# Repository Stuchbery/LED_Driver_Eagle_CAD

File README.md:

# LED_Driver_Eagle_CAD
Led Driver for Light Tower Project

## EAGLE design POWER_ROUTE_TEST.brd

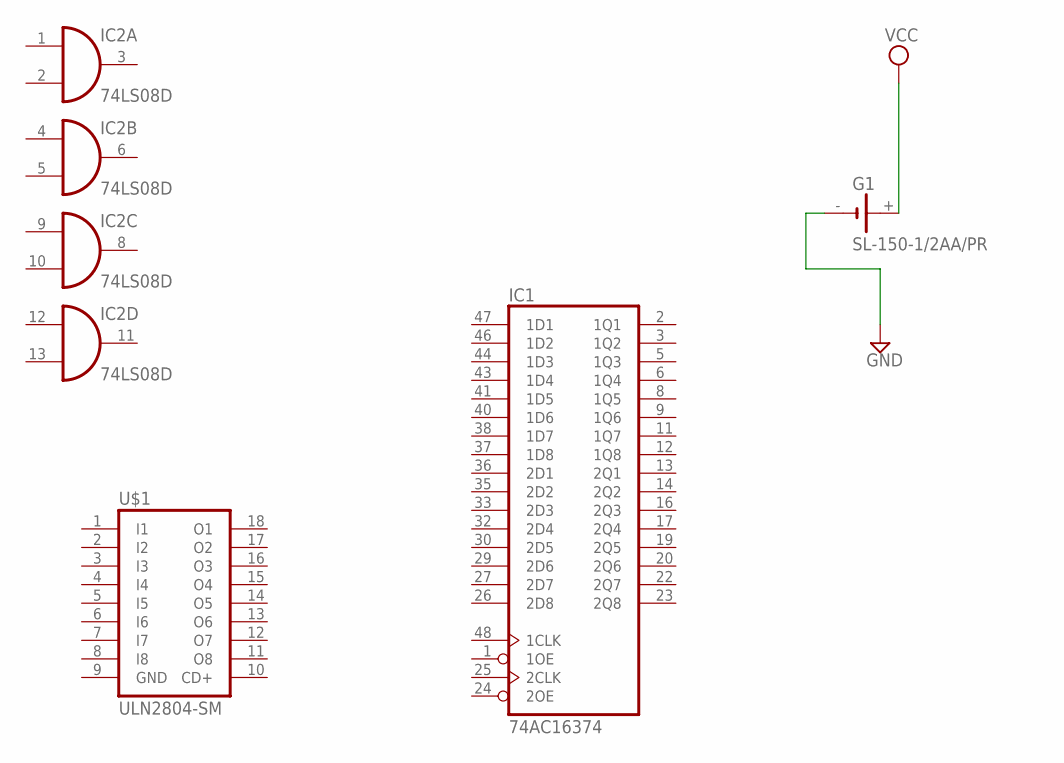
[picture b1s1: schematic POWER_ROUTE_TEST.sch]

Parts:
G1: SL-150-1/2AA/PR
IC1: 74AC16374; SSOP48DL
IC2: 74LS08D; SO14
U$1: ULN2804-SM; SOP-18

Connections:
GND: G1.-, IC1.4 (GND), IC1.10 (GND), IC1.15 (GND), IC1.21 (GND), IC1.28 (GND), IC1.34 (GND), IC1.39 (GND), IC1.45 (GND), IC2.7 (GND), U$1.9 (GND)
VCC: G1.+, IC1.7 (VCC), IC1.18 (VCC), IC1.31 (VCC), IC1.42 (VCC), IC2.14 (VCC)

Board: 2 copper layers, 4 parts (0 on the bottom side), 2 nets, no tracks yet.

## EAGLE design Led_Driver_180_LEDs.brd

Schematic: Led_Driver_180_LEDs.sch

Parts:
IC1, IC3, IC8, IC16, IC21, IC26, IC41, IC46, IC51, IC56, IC101, IC102: 74AC16374; SSOP48DL
IC2, IC4, IC5, IC6, IC7, IC9, IC10, IC11, IC12, IC13, IC14, IC15, IC17, IC18, IC19, IC20, IC22, IC23, IC24, IC25, IC27, IC28, IC29, IC30, IC42, IC43, IC44, IC45, IC47, IC48, IC49, IC50, IC52, IC53, IC54, IC55, IC57, IC58, IC59, IC60: 74S08D; SO14
U$1, U$2, U$3, U$4, U$5, U$6, U$7, U$8, U$9, U$10, U$11, U$12, U$17, U$18, U$19, U$20, U$21, U$22, U$23, U$24: ULN2804-SM; SOP-18
X1, X2, X3, X5, X6: 87758-3216
X11: 87758-1416

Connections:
GND: IC1.1 (1OE), IC1.4 (GND), IC1.10 (GND), IC1.15 (GND), IC1.21 (GND), IC1.24 (2OE), IC1.28 (GND), IC1.34 (GND), IC1.39 (GND), IC1.45 (GND), IC2.7 (GND), IC3.1 (1OE), IC3.4 (GND), IC3.10 (GND), IC3.15 (GND), IC3.21 (GND), IC3.24 (2OE), IC3.28 (GND), IC3.34 (GND), IC3.39 (GND), IC3.45 (GND), IC4.7 (GND), IC5.7 (GND), IC6.7 (GND), IC7.7 (GND), IC8.1 (1OE), IC8.4 (GND), IC8.10 (GND), IC8.15 (GND), IC8.21 (GND), IC8.24 (2OE), IC8.28 (GND), IC8.34 (GND), IC8.39 (GND), IC8.45 (GND), IC9.7 (GND), IC10.7 (GND), IC11.7 (GND), IC12.7 (GND), IC13.7 (GND), IC14.7 (GND), IC15.7 (GND), IC16.1 (1OE), IC16.4 (GND), IC16.10 (GND), IC16.15 (GND), IC16.21 (GND), IC16.24 (2OE), IC16.28 (GND), IC16.34 (GND), IC16.39 (GND), IC16.45 (GND), IC17.7 (GND), IC18.7 (GND), IC19.7 (GND), IC20.7 (GND), IC21.1 (1OE), IC21.4 (GND), IC21.10 (GND), IC21.15 (GND), IC21.21 (GND), IC21.24 (2OE), IC21.28 (GND), IC21.34 (GND), IC21.39 (GND), IC21.45 (GND), IC22.7 (GND), IC23.7 (GND), IC24.7 (GND), IC25.7 (GND), IC26.1 (1OE), IC26.4 (GND), IC26.10 (GND), IC26.15 (GND), IC26.21 (GND), IC26.24 (2OE), IC26.28 (GND), IC26.34 (GND), IC26.39 (GND), IC26.45 (GND), IC27.7 (GND), IC28.7 (GND), IC29.7 (GND), IC30.7 (GND), IC41.1 (1OE), IC41.4 (GND), IC41.10 (GND), IC41.15 (GND), IC41.21 (GND), IC41.24 (2OE), IC41.28 (GND), IC41.34 (GND), IC41.39 (GND), IC41.45 (GND), IC42.7 (GND), IC43.7 (GND), IC44.7 (GND), IC45.7 (GND), IC46.1 (1OE), IC46.4 (GND), IC46.10 (GND), IC46.15 (GND), IC46.21 (GND), IC46.24 (2OE), IC46.28 (GND), IC46.34 (GND), IC46.39 (GND), IC46.45 (GND), IC47.7 (GND), IC48.7 (GND), IC49.7 (GND), IC50.7 (GND), IC51.1 (1OE), IC51.4 (GND), IC51.10 (GND), IC51.15 (GND), IC51.21 (GND), IC51.24 (2OE), IC51.28 (GND), IC51.34 (GND), IC51.39 (GND), IC51.45 (GND), IC52.7 (GND), IC53.7 (GND), IC54.7 (GND), IC55.7 (GND), IC56.1 (1OE), IC56.4 (GND), IC56.10 (GND), IC56.15 (GND), IC56.21 (GND), IC56.24 (2OE), IC56.28 (GND), IC56.34 (GND), IC56.39 (GND), IC56.45 (GND), IC57.7 (GND), IC58.7 (GND), IC59.7 (GND), IC60.7 (GND), IC101.1 (1OE), IC101.4 (GND), IC101.10 (GND), IC101.15 (GND), IC101.21 (GND), IC101.24 (2OE), IC101.28 (GND), IC101.34 (GND), IC101.39 (GND), IC101.45 (GND), IC102.1 (1OE), IC102.4 (GND), IC102.10 (GND), IC102.15 (GND), IC102.21 (GND), IC102.24 (2OE), IC102.28 (GND), IC102.34 (GND), IC102.39 (GND), IC102.45 (GND), U$1.9 (GND), U$2.9 (GND), U$3.9 (GND), U$4.9 (GND), U$5.9 (GND), U$6.9 (GND), U$7.9 (GND), U$8.9 (GND), U$9.9 (GND), U$10.9 (GND), U$11.9 (GND), U$12.9 (GND), U$17.9 (GND), U$18.9 (GND), U$19.9 (GND), U$20.9 (GND), U$21.9 (GND), U$22.9 (GND), U$23.9 (GND), U$24.9 (GND), X11.9
unnamed: IC46.23 (2Q8), IC50.12 (I0), X11.2
unnamed: IC1.2 (1Q1), IC1.46 (1D2), IC2.1 (I0)
unnamed: IC1.3 (1Q2), IC1.44 (1D3), IC2.4 (I0)
unnamed: IC1.5 (1Q3), IC1.43 (1D4), IC2.9 (I0)
unnamed: IC1.6 (1Q4), IC1.41 (1D5), IC2.12 (I0)
unnamed: IC1.8 (1Q5), IC1.40 (1D6), IC4.1 (I0)
unnamed: IC1.9 (1Q6), IC1.38 (1D7), IC4.4 (I0)
unnamed: IC1.11 (1Q7), IC1.37 (1D8), IC4.9 (I0)
unnamed: IC1.12 (1Q8), IC1.36 (2D1), IC4.12 (I0)
unnamed: IC1.13 (2Q1), IC1.35 (2D2), IC5.1 (I0)
unnamed: IC1.14 (2Q2), IC1.33 (2D3), IC5.4 (I0)
unnamed: IC1.16 (2Q3), IC1.32 (2D4), IC5.9 (I0)
unnamed: IC1.17 (2Q4), IC1.30 (2D5), IC5.12 (I0)
unnamed: IC1.19 (2Q5), IC1.29 (2D6), IC6.1 (I0)
unnamed: IC1.20 (2Q6), IC1.27 (2D7), IC6.4 (I0)
unnamed: IC1.22 (2Q7), IC1.26 (2D8), IC6.9 (I0)
unnamed: U$1.18 (O1), X2.1
unnamed: IC2.3 (O), U$1.1 (I1)
unnamed: IC2.6 (O), U$1.2 (I2)
unnamed: IC2.8 (O), U$1.3 (I3)
unnamed: IC2.11 (O), U$1.4 (I4)
unnamed: IC4.3 (O), U$1.5 (I5)
unnamed: IC4.11 (O), U$1.8 (I8)
unnamed: IC4.8 (O), U$1.7 (I7)
unnamed: IC4.6 (O), U$1.6 (I6)
unnamed: IC5.3 (O), U$2.1 (I1)
unnamed: IC5.6 (O), U$2.2 (I2)
unnamed: IC5.8 (O), U$2.3 (I3)
unnamed: IC6.11 (O), U$2.8 (I8)
unnamed: IC6.8 (O), U$2.7 (I7)
unnamed: IC6.6 (O), U$2.6 (I6)
unnamed: IC6.3 (O), U$2.5 (I5)
unnamed: IC5.11 (O), U$2.4 (I4)
unnamed: IC22.2 (I1), IC22.5 (I1), IC22.10 (I1), IC22.13 (I1), IC23.2 (I1), IC23.5 (I1), IC23.10 (I1), IC23.13 (I1), IC101.2 (1Q1), IC101.46 (1D2)
unnamed: IC24.2 (I1), IC24.5 (I1), IC24.10 (I1), IC24.13 (I1), IC25.2 (I1), IC25.5 (I1), IC25.10 (I1), IC25.13 (I1), IC101.3 (1Q2), IC101.44 (1D3)
unnamed: IC8.2 (1Q1), IC8.46 (1D2), IC9.1 (I0)
unnamed: IC8.3 (1Q2), IC8.44 (1D3), IC9.4 (I0)
unnamed: IC8.5 (1Q3), IC8.43 (1D4), IC9.9 (I0)
unnamed: IC8.6 (1Q4), IC8.41 (1D5), IC9.12 (I0)
unnamed: IC8.8 (1Q5), IC8.40 (1D6), IC11.1 (I0)
unnamed: IC8.9 (1Q6), IC8.38 (1D7), IC11.4 (I0)
unnamed: IC8.11 (1Q7), IC8.37 (1D8), IC11.9 (I0)
unnamed: IC8.12 (1Q8), IC8.36 (2D1), IC11.12 (I0)
unnamed: IC8.13 (2Q1), IC8.35 (2D2), IC12.1 (I0)
unnamed: IC8.14 (2Q2), IC8.33 (2D3), IC12.4 (I0)
unnamed: IC8.16 (2Q3), IC8.32 (2D4), IC12.9 (I0)
unnamed: IC8.17 (2Q4), IC8.30 (2D5), IC12.12 (I0)
unnamed: IC8.19 (2Q5), IC8.29 (2D6), IC13.1 (I0)
unnamed: IC8.20 (2Q6), IC8.27 (2D7), IC13.4 (I0)
unnamed: IC8.22 (2Q7), IC8.26 (2D8), IC13.9 (I0)
unnamed: IC8.23 (2Q8), IC13.12 (I0), IC51.47 (1D1)
unnamed: IC9.3 (O), U$3.1 (I1)
unnamed: IC9.6 (O), U$3.2 (I2)
unnamed: IC9.8 (O), U$3.3 (I3)
unnamed: IC9.11 (O), U$3.4 (I4)
unnamed: IC11.3 (O), U$3.5 (I5)
unnamed: IC11.11 (O), U$3.8 (I8)
unnamed: IC11.8 (O), U$3.7 (I7)
unnamed: IC11.6 (O), U$3.6 (I6)
unnamed: IC12.3 (O), U$4.1 (I1)
unnamed: IC12.6 (O), U$4.2 (I2)
unnamed: IC12.8 (O), U$4.3 (I3)
unnamed: IC13.11 (O), U$4.8 (I8)
unnamed: IC13.8 (O), U$4.7 (I7)
unnamed: IC13.6 (O), U$4.6 (I6)
unnamed: IC13.3 (O), U$4.5 (I5)
unnamed: IC12.11 (O), U$4.4 (I4)
unnamed: IC1.23 (2Q8), IC6.12 (I0), IC8.47 (1D1)
unnamed: U$1.17 (O2), X2.3
unnamed: U$1.16 (O3), X2.5
unnamed: U$1.15 (O4), X2.7
unnamed: U$1.14 (O5), X2.9
unnamed: U$1.13 (O6), X2.11
unnamed: U$1.12 (O7), X2.13
unnamed: U$1.11 (O8), X2.15
unnamed: U$2.18 (O1), X2.17
unnamed: U$2.17 (O2), X2.19
unnamed: U$2.16 (O3), X2.21
unnamed: U$2.15 (O4), X2.23
unnamed: U$2.14 (O5), X2.25
unnamed: U$2.13 (O6), X2.27
unnamed: U$2.12 (O7), X2.29
unnamed: U$2.11 (O8), X2.31
unnamed: U$4.11 (O8), X2.32
unnamed: U$4.12 (O7), X2.30
unnamed: U$4.13 (O6), X2.28
unnamed: U$4.14 (O5), X2.26
unnamed: U$4.15 (O4), X2.24
unnamed: U$4.16 (O3), X2.22
unnamed: U$4.17 (O2), X2.20
unnamed: U$4.18 (O1), X2.18
unnamed: U$3.11 (O8), X2.16
unnamed: U$3.12 (O7), X2.14
unnamed: U$3.13 (O6), X2.12
unnamed: U$3.14 (O5), X2.10
unnamed: U$3.15 (O4), X2.8
unnamed: U$3.16 (O3), X2.6
unnamed: U$3.17 (O2), X2.4
unnamed: U$3.18 (O1), X2.2
unnamed: IC3.2 (1Q1), IC3.46 (1D2), IC7.1 (I0)
unnamed: IC3.3 (1Q2), IC3.44 (1D3), IC7.4 (I0)
unnamed: IC3.5 (1Q3), IC3.43 (1D4), IC7.9 (I0)
unnamed: IC3.6 (1Q4), IC3.41 (1D5), IC7.12 (I0)
unnamed: IC3.8 (1Q5), IC3.40 (1D6), IC10.1 (I0)
unnamed: IC3.9 (1Q6), IC3.38 (1D7), IC10.4 (I0)
unnamed: IC3.11 (1Q7), IC3.37 (1D8), IC10.9 (I0)
unnamed: IC3.12 (1Q8), IC3.36 (2D1), IC10.12 (I0)
unnamed: IC3.13 (2Q1), IC3.35 (2D2), IC14.1 (I0)
unnamed: IC3.14 (2Q2), IC3.33 (2D3), IC14.4 (I0)
unnamed: IC3.16 (2Q3), IC3.32 (2D4), IC14.9 (I0)
unnamed: IC3.17 (2Q4), IC3.30 (2D5), IC14.12 (I0)
unnamed: IC3.19 (2Q5), IC3.29 (2D6), IC15.1 (I0)
unnamed: IC3.20 (2Q6), IC3.27 (2D7), IC15.4 (I0)
unnamed: IC3.22 (2Q7), IC3.26 (2D8), IC15.9 (I0)
unnamed: IC7.3 (O), U$5.1 (I1)
unnamed: IC7.6 (O), U$5.2 (I2)
unnamed: IC7.8 (O), U$5.3 (I3)
unnamed: IC7.11 (O), U$5.4 (I4)
unnamed: IC10.3 (O), U$5.5 (I5)
unnamed: IC10.11 (O), U$5.8 (I8)
unnamed: IC10.8 (O), U$5.7 (I7)
unnamed: IC10.6 (O), U$5.6 (I6)
unnamed: IC14.3 (O), U$6.1 (I1)
unnamed: IC14.6 (O), U$6.2 (I2)
unnamed: IC14.8 (O), U$6.3 (I3)
unnamed: IC15.11 (O), U$6.8 (I8)
unnamed: IC15.8 (O), U$6.7 (I7)
unnamed: IC15.6 (O), U$6.6 (I6)
unnamed: IC15.3 (O), U$6.5 (I5)
unnamed: IC14.11 (O), U$6.4 (I4)
unnamed: IC16.2 (1Q1), IC16.46 (1D2), IC17.1 (I0)
unnamed: IC16.3 (1Q2), IC16.44 (1D3), IC17.4 (I0)
unnamed: IC16.5 (1Q3), IC16.43 (1D4), IC17.9 (I0)
unnamed: IC16.6 (1Q4), IC16.41 (1D5), IC17.12 (I0)
unnamed: IC16.8 (1Q5), IC16.40 (1D6), IC18.1 (I0)
unnamed: IC16.9 (1Q6), IC16.38 (1D7), IC18.4 (I0)
unnamed: IC16.11 (1Q7), IC16.37 (1D8), IC18.9 (I0)
unnamed: IC16.12 (1Q8), IC16.36 (2D1), IC18.12 (I0)
unnamed: IC16.13 (2Q1), IC16.35 (2D2), IC19.1 (I0)
unnamed: IC16.14 (2Q2), IC16.33 (2D3), IC19.4 (I0)
unnamed: IC16.16 (2Q3), IC16.32 (2D4), IC19.9 (I0)
unnamed: IC16.17 (2Q4), IC16.30 (2D5), IC19.12 (I0)
unnamed: IC16.19 (2Q5), IC16.29 (2D6), IC20.1 (I0)
unnamed: IC16.20 (2Q6), IC16.27 (2D7), IC20.4 (I0)
unnamed: IC16.22 (2Q7), IC16.26 (2D8), IC20.9 (I0)
unnamed: IC1.47 (1D1), IC16.23 (2Q8), IC20.12 (I0)
unnamed: IC17.3 (O), U$7.1 (I1)
unnamed: IC17.6 (O), U$7.2 (I2)
unnamed: IC17.8 (O), U$7.3 (I3)
unnamed: IC17.11 (O), U$7.4 (I4)
unnamed: IC18.3 (O), U$7.5 (I5)
unnamed: IC18.11 (O), U$7.8 (I8)
unnamed: IC18.8 (O), U$7.7 (I7)
unnamed: IC18.6 (O), U$7.6 (I6)
unnamed: IC19.3 (O), U$8.1 (I1)
unnamed: IC19.6 (O), U$8.2 (I2)
unnamed: IC19.8 (O), U$8.3 (I3)
unnamed: IC20.11 (O), U$8.8 (I8)
unnamed: IC20.8 (O), U$8.7 (I7)
unnamed: IC20.6 (O), U$8.6 (I6)
unnamed: IC20.3 (O), U$8.5 (I5)
unnamed: IC19.11 (O), U$8.4 (I4)
unnamed: IC3.23 (2Q8), IC15.12 (I0), IC16.47 (1D1)
unnamed: U$5.18 (O1), X1.1
unnamed: U$5.17 (O2), X1.3
unnamed: U$5.16 (O3), X1.5
unnamed: U$5.15 (O4), X1.7
unnamed: U$5.14 (O5), X1.9
unnamed: U$5.13 (O6), X1.11
unnamed: U$5.12 (O7), X1.13
unnamed: U$5.11 (O8), X1.15
unnamed: U$6.18 (O1), X1.17
unnamed: U$6.17 (O2), X1.19
unnamed: U$6.16 (O3), X1.21
unnamed: U$6.15 (O4), X1.23
unnamed: U$6.14 (O5), X1.25
unnamed: U$6.13 (O6), X1.27
unnamed: U$6.12 (O7), X1.29
unnamed: U$6.11 (O8), X1.31
unnamed: U$8.11 (O8), X1.32
unnamed: U$8.12 (O7), X1.30
unnamed: U$8.13 (O6), X1.28
unnamed: U$8.14 (O5), X1.26
unnamed: U$8.15 (O4), X1.24
unnamed: U$8.16 (O3), X1.22
unnamed: U$8.17 (O2), X1.20
unnamed: U$8.18 (O1), X1.18
unnamed: U$7.11 (O8), X1.16
unnamed: U$7.12 (O7), X1.14
unnamed: U$7.13 (O6), X1.12
unnamed: U$7.14 (O5), X1.10
unnamed: U$7.15 (O4), X1.8
unnamed: U$7.16 (O3), X1.6
unnamed: U$7.17 (O2), X1.4
unnamed: U$7.18 (O1), X1.2
unnamed: IC21.2 (1Q1), IC21.46 (1D2), IC22.1 (I0)
unnamed: IC21.3 (1Q2), IC21.44 (1D3), IC22.4 (I0)
unnamed: IC21.5 (1Q3), IC21.43 (1D4), IC22.9 (I0)
unnamed: IC21.6 (1Q4), IC21.41 (1D5), IC22.12 (I0)
unnamed: IC21.8 (1Q5), IC21.40 (1D6), IC23.1 (I0)
unnamed: IC21.9 (1Q6), IC21.38 (1D7), IC23.4 (I0)
unnamed: IC21.11 (1Q7), IC21.37 (1D8), IC23.9 (I0)
unnamed: IC21.12 (1Q8), IC21.36 (2D1), IC23.12 (I0)
unnamed: IC21.13 (2Q1), IC21.35 (2D2), IC24.1 (I0)
unnamed: IC21.14 (2Q2), IC21.33 (2D3), IC24.4 (I0)
unnamed: IC21.16 (2Q3), IC21.32 (2D4), IC24.9 (I0)
unnamed: IC21.17 (2Q4), IC21.30 (2D5), IC24.12 (I0)
unnamed: IC21.19 (2Q5), IC21.29 (2D6), IC25.1 (I0)
unnamed: IC21.20 (2Q6), IC21.27 (2D7), IC25.4 (I0)
unnamed: IC21.22 (2Q7), IC21.26 (2D8), IC25.9 (I0)
unnamed: IC22.3 (O), U$9.1 (I1)
unnamed: IC22.6 (O), U$9.2 (I2)
unnamed: IC22.8 (O), U$9.3 (I3)
unnamed: IC22.11 (O), U$9.4 (I4)
unnamed: IC23.3 (O), U$9.5 (I5)
unnamed: IC23.11 (O), U$9.8 (I8)
unnamed: IC23.8 (O), U$9.7 (I7)
unnamed: IC23.6 (O), U$9.6 (I6)
unnamed: IC24.3 (O), U$10.1 (I1)
unnamed: IC24.6 (O), U$10.2 (I2)
unnamed: IC24.8 (O), U$10.3 (I3)
unnamed: IC25.11 (O), U$10.8 (I8)
unnamed: IC25.8 (O), U$10.7 (I7)
unnamed: IC25.6 (O), U$10.6 (I6)
unnamed: IC25.3 (O), U$10.5 (I5)
unnamed: IC24.11 (O), U$10.4 (I4)
unnamed: IC21.47 (1D1), X11.4
unnamed: IC26.2 (1Q1), IC26.46 (1D2), IC27.1 (I0)
unnamed: IC26.3 (1Q2), IC26.44 (1D3), IC27.4 (I0)
unnamed: IC26.5 (1Q3), IC26.43 (1D4), IC27.9 (I0)
unnamed: IC26.6 (1Q4), IC26.41 (1D5), IC27.12 (I0)
unnamed: IC26.8 (1Q5), IC26.40 (1D6), IC28.1 (I0)
unnamed: IC26.9 (1Q6), IC26.38 (1D7), IC28.4 (I0)
unnamed: IC26.11 (1Q7), IC26.37 (1D8), IC28.9 (I0)
unnamed: IC26.12 (1Q8), IC26.36 (2D1), IC28.12 (I0)
unnamed: IC26.13 (2Q1), IC26.35 (2D2), IC29.1 (I0)
unnamed: IC26.14 (2Q2), IC26.33 (2D3), IC29.4 (I0)
unnamed: IC26.16 (2Q3), IC26.32 (2D4), IC29.9 (I0)
unnamed: IC26.17 (2Q4), IC26.30 (2D5), IC29.12 (I0)
unnamed: IC26.19 (2Q5), IC26.29 (2D6), IC30.1 (I0)
unnamed: IC26.20 (2Q6), IC26.27 (2D7), IC30.4 (I0)
unnamed: IC26.22 (2Q7), IC26.26 (2D8), IC30.9 (I0)
unnamed: IC3.47 (1D1), IC26.23 (2Q8), IC30.12 (I0)
unnamed: IC27.3 (O), U$11.1 (I1)
unnamed: IC27.6 (O), U$11.2 (I2)
unnamed: IC27.8 (O), U$11.3 (I3)
unnamed: IC27.11 (O), U$11.4 (I4)
unnamed: IC28.3 (O), U$11.5 (I5)
unnamed: IC28.11 (O), U$11.8 (I8)
unnamed: IC28.8 (O), U$11.7 (I7)
unnamed: IC28.6 (O), U$11.6 (I6)
unnamed: IC29.3 (O), U$12.1 (I1)
unnamed: IC29.6 (O), U$12.2 (I2)
unnamed: IC29.8 (O), U$12.3 (I3)
unnamed: IC30.11 (O), U$12.8 (I8)
unnamed: IC30.8 (O), U$12.7 (I7)
unnamed: IC30.6 (O), U$12.6 (I6)
unnamed: IC30.3 (O), U$12.5 (I5)
unnamed: IC29.11 (O), U$12.4 (I4)
unnamed: IC21.23 (2Q8), IC25.12 (I0), IC26.47 (1D1)
unnamed: U$9.18 (O1), X3.1
unnamed: U$9.17 (O2), X3.3
unnamed: U$9.16 (O3), X3.5
unnamed: U$9.15 (O4), X3.7
unnamed: U$9.14 (O5), X3.9
unnamed: U$9.13 (O6), X3.11
unnamed: U$9.12 (O7), X3.13
unnamed: U$9.11 (O8), X3.15
unnamed: U$10.18 (O1), X3.17
unnamed: U$10.17 (O2), X3.19
unnamed: U$10.16 (O3), X3.21
unnamed: U$10.15 (O4), X3.23
unnamed: U$10.14 (O5), X3.25
unnamed: U$10.13 (O6), X3.27
unnamed: U$10.12 (O7), X3.29
unnamed: U$10.11 (O8), X3.31
unnamed: U$12.11 (O8), X3.32
unnamed: U$12.12 (O7), X3.30
unnamed: U$12.13 (O6), X3.28
unnamed: U$12.14 (O5), X3.26
unnamed: U$12.15 (O4), X3.24
unnamed: U$12.16 (O3), X3.22
unnamed: U$12.17 (O2), X3.20
unnamed: U$12.18 (O1), X3.18
unnamed: U$11.11 (O8), X3.16
unnamed: U$11.12 (O7), X3.14
unnamed: U$11.13 (O6), X3.12
unnamed: U$11.14 (O5), X3.10
unnamed: U$11.15 (O4), X3.8
unnamed: U$11.16 (O3), X3.6
unnamed: U$11.17 (O2), X3.4
unnamed: U$11.18 (O1), X3.2
unnamed: IC41.2 (1Q1), IC41.46 (1D2), IC42.1 (I0)
unnamed: IC41.3 (1Q2), IC41.44 (1D3), IC42.4 (I0)
unnamed: IC41.5 (1Q3), IC41.43 (1D4), IC42.9 (I0)
unnamed: IC41.6 (1Q4), IC41.41 (1D5), IC42.12 (I0)
unnamed: IC41.8 (1Q5), IC41.40 (1D6), IC43.1 (I0)
unnamed: IC41.9 (1Q6), IC41.38 (1D7), IC43.4 (I0)
unnamed: IC41.11 (1Q7), IC41.37 (1D8), IC43.9 (I0)
unnamed: IC41.12 (1Q8), IC41.36 (2D1), IC43.12 (I0)
unnamed: IC41.13 (2Q1), IC41.35 (2D2), IC44.1 (I0)
unnamed: IC41.14 (2Q2), IC41.33 (2D3), IC44.4 (I0)
unnamed: IC41.16 (2Q3), IC41.32 (2D4), IC44.9 (I0)
unnamed: IC41.17 (2Q4), IC41.30 (2D5), IC44.12 (I0)
unnamed: IC41.19 (2Q5), IC41.29 (2D6), IC45.1 (I0)
unnamed: IC41.20 (2Q6), IC41.27 (2D7), IC45.4 (I0)
unnamed: IC41.22 (2Q7), IC41.26 (2D8), IC45.9 (I0)
unnamed: IC42.3 (O), U$17.1 (I1)
unnamed: IC42.6 (O), U$17.2 (I2)
unnamed: IC42.8 (O), U$17.3 (I3)
unnamed: IC42.11 (O), U$17.4 (I4)
unnamed: IC43.3 (O), U$17.5 (I5)
unnamed: IC43.11 (O), U$17.8 (I8)
unnamed: IC43.8 (O), U$17.7 (I7)
unnamed: IC43.6 (O), U$17.6 (I6)
unnamed: IC44.3 (O), U$18.1 (I1)
unnamed: IC44.6 (O), U$18.2 (I2)
unnamed: IC44.8 (O), U$18.3 (I3)
unnamed: IC45.11 (O), U$18.8 (I8)
unnamed: IC45.8 (O), U$18.7 (I7)
unnamed: IC45.6 (O), U$18.6 (I6)
unnamed: IC45.3 (O), U$18.5 (I5)
unnamed: IC44.11 (O), U$18.4 (I4)
unnamed: IC46.2 (1Q1), IC46.46 (1D2), IC47.1 (I0)
unnamed: IC46.3 (1Q2), IC46.44 (1D3), IC47.4 (I0)
unnamed: IC46.5 (1Q3), IC46.43 (1D4), IC47.9 (I0)
unnamed: IC46.6 (1Q4), IC46.41 (1D5), IC47.12 (I0)
unnamed: IC46.8 (1Q5), IC46.40 (1D6), IC48.1 (I0)
unnamed: IC46.9 (1Q6), IC46.38 (1D7), IC48.4 (I0)
unnamed: IC46.11 (1Q7), IC46.37 (1D8), IC48.9 (I0)
unnamed: IC46.12 (1Q8), IC46.36 (2D1), IC48.12 (I0)
unnamed: IC46.13 (2Q1), IC46.35 (2D2), IC49.1 (I0)
unnamed: IC46.14 (2Q2), IC46.33 (2D3), IC49.4 (I0)
unnamed: IC46.16 (2Q3), IC46.32 (2D4), IC49.9 (I0)
unnamed: IC46.17 (2Q4), IC46.30 (2D5), IC49.12 (I0)
unnamed: IC46.19 (2Q5), IC46.29 (2D6), IC50.1 (I0)
unnamed: IC46.20 (2Q6), IC46.27 (2D7), IC50.4 (I0)
unnamed: IC46.22 (2Q7), IC46.26 (2D8), IC50.9 (I0)
unnamed: IC47.3 (O), U$19.1 (I1)
unnamed: IC47.6 (O), U$19.2 (I2)
unnamed: IC47.8 (O), U$19.3 (I3)
unnamed: IC47.11 (O), U$19.4 (I4)
unnamed: IC48.3 (O), U$19.5 (I5)
unnamed: IC48.11 (O), U$19.8 (I8)
unnamed: IC48.8 (O), U$19.7 (I7)
unnamed: IC48.6 (O), U$19.6 (I6)
unnamed: IC49.3 (O), U$20.1 (I1)
unnamed: IC49.6 (O), U$20.2 (I2)
unnamed: IC49.8 (O), U$20.3 (I3)
unnamed: IC50.11 (O), U$20.8 (I8)
unnamed: IC50.8 (O), U$20.7 (I7)
unnamed: IC50.6 (O), U$20.6 (I6)
unnamed: IC50.3 (O), U$20.5 (I5)
unnamed: IC49.11 (O), U$20.4 (I4)
unnamed: IC41.23 (2Q8), IC45.12 (I0), IC46.47 (1D1)
unnamed: U$17.18 (O1), X5.1
unnamed: U$17.17 (O2), X5.3
unnamed: U$17.16 (O3), X5.5
unnamed: U$17.15 (O4), X5.7
unnamed: U$17.14 (O5), X5.9
unnamed: U$17.13 (O6), X5.11
unnamed: U$17.12 (O7), X5.13
unnamed: U$17.11 (O8), X5.15
unnamed: U$18.18 (O1), X5.17
unnamed: U$18.17 (O2), X5.19
unnamed: U$18.16 (O3), X5.21
unnamed: U$18.15 (O4), X5.23
unnamed: U$18.14 (O5), X5.25
unnamed: U$18.13 (O6), X5.27
unnamed: U$18.12 (O7), X5.29
unnamed: U$18.11 (O8), X5.31
unnamed: U$20.11 (O8), X5.32
unnamed: U$20.12 (O7), X5.30
unnamed: U$20.13 (O6), X5.28
unnamed: U$20.14 (O5), X5.26
unnamed: U$20.15 (O4), X5.24
unnamed: U$20.16 (O3), X5.22
unnamed: U$20.17 (O2), X5.20
unnamed: U$20.18 (O1), X5.18
unnamed: U$19.11 (O8), X5.16
unnamed: U$19.12 (O7), X5.14
unnamed: U$19.13 (O6), X5.12
unnamed: U$19.14 (O5), X5.10
unnamed: U$19.15 (O4), X5.8
unnamed: U$19.16 (O3), X5.6
unnamed: U$19.17 (O2), X5.4
unnamed: U$19.18 (O1), X5.2
unnamed: IC51.2 (1Q1), IC51.46 (1D2), IC52.1 (I0)
unnamed: IC51.3 (1Q2), IC51.44 (1D3), IC52.4 (I0)
unnamed: IC51.5 (1Q3), IC51.43 (1D4), IC52.9 (I0)
unnamed: IC51.6 (1Q4), IC51.41 (1D5), IC52.12 (I0)
unnamed: IC51.8 (1Q5), IC51.40 (1D6), IC53.1 (I0)
unnamed: IC51.9 (1Q6), IC51.38 (1D7), IC53.4 (I0)
unnamed: IC51.11 (1Q7), IC51.37 (1D8), IC53.9 (I0)
unnamed: IC51.12 (1Q8), IC51.36 (2D1), IC53.12 (I0)
unnamed: IC51.13 (2Q1), IC51.35 (2D2), IC54.1 (I0)
unnamed: IC51.14 (2Q2), IC51.33 (2D3), IC54.4 (I0)
unnamed: IC51.16 (2Q3), IC51.32 (2D4), IC54.9 (I0)
unnamed: IC51.17 (2Q4), IC51.30 (2D5), IC54.12 (I0)
unnamed: IC51.19 (2Q5), IC51.29 (2D6), IC55.1 (I0)
unnamed: IC51.20 (2Q6), IC51.27 (2D7), IC55.4 (I0)
unnamed: IC51.22 (2Q7), IC51.26 (2D8), IC55.9 (I0)
unnamed: IC52.3 (O), U$21.1 (I1)
unnamed: IC52.6 (O), U$21.2 (I2)
unnamed: IC52.8 (O), U$21.3 (I3)
unnamed: IC52.11 (O), U$21.4 (I4)
unnamed: IC53.3 (O), U$21.5 (I5)
unnamed: IC53.11 (O), U$21.8 (I8)
unnamed: IC53.8 (O), U$21.7 (I7)
unnamed: IC53.6 (O), U$21.6 (I6)
unnamed: IC54.3 (O), U$22.1 (I1)
unnamed: IC54.6 (O), U$22.2 (I2)
unnamed: IC54.8 (O), U$22.3 (I3)
unnamed: IC55.11 (O), U$22.8 (I8)
unnamed: IC55.8 (O), U$22.7 (I7)
unnamed: IC55.6 (O), U$22.6 (I6)
unnamed: IC55.3 (O), U$22.5 (I5)
unnamed: IC54.11 (O), U$22.4 (I4)
unnamed: IC56.2 (1Q1), IC56.46 (1D2), IC57.1 (I0)
unnamed: IC56.3 (1Q2), IC56.44 (1D3), IC57.4 (I0)
unnamed: IC56.5 (1Q3), IC56.43 (1D4), IC57.9 (I0)
unnamed: IC56.6 (1Q4), IC56.41 (1D5), IC57.12 (I0)
unnamed: IC56.8 (1Q5), IC56.40 (1D6), IC58.1 (I0)
unnamed: IC56.9 (1Q6), IC56.38 (1D7), IC58.4 (I0)
unnamed: IC56.11 (1Q7), IC56.37 (1D8), IC58.9 (I0)
unnamed: IC56.12 (1Q8), IC56.36 (2D1), IC58.12 (I0)
unnamed: IC56.13 (2Q1), IC56.35 (2D2), IC59.1 (I0)
unnamed: IC56.14 (2Q2), IC56.33 (2D3), IC59.4 (I0)
unnamed: IC56.16 (2Q3), IC56.32 (2D4), IC59.9 (I0)
unnamed: IC56.17 (2Q4), IC56.30 (2D5), IC59.12 (I0)
unnamed: IC56.19 (2Q5), IC56.29 (2D6), IC60.1 (I0)
unnamed: IC56.20 (2Q6), IC56.27 (2D7), IC60.4 (I0)
unnamed: IC56.22 (2Q7), IC56.26 (2D8), IC60.9 (I0)
unnamed: IC41.47 (1D1), IC56.23 (2Q8), IC60.12 (I0)
unnamed: IC57.3 (O), U$23.1 (I1)
unnamed: IC57.6 (O), U$23.2 (I2)
unnamed: IC57.8 (O), U$23.3 (I3)
unnamed: IC57.11 (O), U$23.4 (I4)
unnamed: IC58.3 (O), U$23.5 (I5)
unnamed: IC58.11 (O), U$23.8 (I8)
unnamed: IC58.8 (O), U$23.7 (I7)
unnamed: IC58.6 (O), U$23.6 (I6)
unnamed: IC59.3 (O), U$24.1 (I1)
unnamed: IC59.6 (O), U$24.2 (I2)
unnamed: IC59.8 (O), U$24.3 (I3)
unnamed: IC60.11 (O), U$24.8 (I8)
unnamed: IC60.8 (O), U$24.7 (I7)
unnamed: IC60.6 (O), U$24.6 (I6)
unnamed: IC60.3 (O), U$24.5 (I5)
unnamed: IC59.11 (O), U$24.4 (I4)
unnamed: IC51.23 (2Q8), IC55.12 (I0), IC56.47 (1D1)
unnamed: U$21.18 (O1), X6.1
unnamed: U$21.17 (O2), X6.3
unnamed: U$21.16 (O3), X6.5
unnamed: U$21.15 (O4), X6.7
unnamed: U$21.14 (O5), X6.9
unnamed: U$21.13 (O6), X6.11
unnamed: U$21.12 (O7), X6.13
unnamed: U$21.11 (O8), X6.15
unnamed: U$22.18 (O1), X6.17
unnamed: U$22.17 (O2), X6.19
unnamed: U$22.16 (O3), X6.21
unnamed: U$22.15 (O4), X6.23
unnamed: U$22.14 (O5), X6.25
unnamed: U$22.13 (O6), X6.27
unnamed: U$22.12 (O7), X6.29
unnamed: U$22.11 (O8), X6.31
unnamed: U$24.11 (O8), X6.32
unnamed: U$24.12 (O7), X6.30
unnamed: U$24.13 (O6), X6.28
unnamed: U$24.14 (O5), X6.26
unnamed: U$24.15 (O4), X6.24
unnamed: U$24.16 (O3), X6.22
unnamed: U$24.17 (O2), X6.20
unnamed: U$24.18 (O1), X6.18
unnamed: U$23.11 (O8), X6.16
unnamed: U$23.12 (O7), X6.14
unnamed: U$23.13 (O6), X6.12
unnamed: U$23.14 (O5), X6.10
unnamed: U$23.15 (O4), X6.8
unnamed: U$23.16 (O3), X6.6
unnamed: U$23.17 (O2), X6.4
unnamed: U$23.18 (O1), X6.2
unnamed: IC27.2 (I1), IC27.5 (I1), IC27.10 (I1), IC27.13 (I1), IC28.2 (I1), IC28.5 (I1), IC28.10 (I1), IC28.13 (I1), IC101.5 (1Q3), IC101.43 (1D4)
unnamed: IC29.2 (I1), IC29.5 (I1), IC29.10 (I1), IC29.13 (I1), IC30.2 (I1), IC30.5 (I1), IC30.10 (I1), IC30.13 (I1), IC101.6 (1Q4), IC101.41 (1D5)
unnamed: IC7.2 (I1), IC7.5 (I1), IC7.10 (I1), IC7.13 (I1), IC10.2 (I1), IC10.5 (I1), IC10.10 (I1), IC10.13 (I1), IC101.8 (1Q5), IC101.40 (1D6)
unnamed: IC14.2 (I1), IC14.5 (I1), IC14.10 (I1), IC14.13 (I1), IC15.2 (I1), IC15.5 (I1), IC15.10 (I1), IC15.13 (I1), IC101.9 (1Q6), IC101.38 (1D7)
unnamed: IC17.2 (I1), IC17.5 (I1), IC17.10 (I1), IC17.13 (I1), IC18.2 (I1), IC18.5 (I1), IC18.10 (I1), IC18.13 (I1), IC101.11 (1Q7), IC101.37 (1D8)
unnamed: IC19.2 (I1), IC19.5 (I1), IC19.10 (I1), IC19.13 (I1), IC20.2 (I1), IC20.5 (I1), IC20.10 (I1), IC20.13 (I1), IC101.12 (1Q8), IC101.36 (2D1)
unnamed: IC2.2 (I1), IC2.5 (I1), IC2.10 (I1), IC2.13 (I1), IC4.2 (I1), IC4.5 (I1), IC4.10 (I1), IC4.13 (I1), IC101.13 (2Q1), IC101.35 (2D2)
unnamed: IC5.2 (I1), IC5.5 (I1), IC5.10 (I1), IC5.13 (I1), IC6.2 (I1), IC6.5 (I1), IC6.10 (I1), IC6.13 (I1), IC101.14 (2Q2), IC101.33 (2D3)
unnamed: IC9.2 (I1), IC9.5 (I1), IC9.10 (I1), IC9.13 (I1), IC11.2 (I1), IC11.5 (I1), IC11.10 (I1), IC11.13 (I1), IC101.16 (2Q3), IC101.32 (2D4)
unnamed: IC12.2 (I1), IC12.5 (I1), IC12.10 (I1), IC12.13 (I1), IC13.2 (I1), IC13.5 (I1), IC13.10 (I1), IC13.13 (I1), IC101.17 (2Q4), IC101.30 (2D5)
unnamed: IC52.2 (I1), IC52.5 (I1), IC52.10 (I1), IC52.13 (I1), IC53.2 (I1), IC53.5 (I1), IC53.10 (I1), IC53.13 (I1), IC101.19 (2Q5), IC101.29 (2D6)
unnamed: IC54.2 (I1), IC54.5 (I1), IC54.10 (I1), IC54.13 (I1), IC55.2 (I1), IC55.5 (I1), IC55.10 (I1), IC55.13 (I1), IC101.20 (2Q6), IC101.27 (2D7)
unnamed: IC57.2 (I1), IC57.5 (I1), IC57.10 (I1), IC57.13 (I1), IC58.2 (I1), IC58.5 (I1), IC58.10 (I1), IC58.13 (I1), IC101.22 (2Q7), IC101.26 (2D8)
unnamed: IC59.2 (I1), IC59.5 (I1), IC59.10 (I1), IC59.13 (I1), IC60.2 (I1), IC60.5 (I1), IC60.10 (I1), IC60.13 (I1), IC101.23 (2Q8), IC102.47 (1D1)
unnamed: IC101.47 (1D1), X11.3
unnamed: U$1.10 (CD+), U$2.10 (CD+), U$3.10 (CD+), U$4.10 (CD+), U$5.10 (CD+), U$6.10 (CD+), U$7.10 (CD+), U$8.10 (CD+), U$9.10 (CD+), U$10.10 (CD+), U$11.10 (CD+), U$12.10 (CD+), U$17.10 (CD+), U$18.10 (CD+), U$19.10 (CD+), U$20.10 (CD+), U$21.10 (CD+), U$22.10 (CD+), U$23.10 (CD+), U$24.10 (CD+), X11.7
unnamed: IC42.2 (I1), IC42.5 (I1), IC42.10 (I1), IC42.13 (I1), IC43.2 (I1), IC43.5 (I1), IC43.10 (I1), IC43.13 (I1), IC102.2 (1Q1), IC102.46 (1D2)
unnamed: IC44.2 (I1), IC44.5 (I1), IC44.10 (I1), IC44.13 (I1), IC45.2 (I1), IC45.5 (I1), IC45.10 (I1), IC45.13 (I1), IC102.3 (1Q2), IC102.44 (1D3)
unnamed: IC47.2 (I1), IC47.5 (I1), IC47.10 (I1), IC47.13 (I1), IC48.2 (I1), IC48.5 (I1), IC48.10 (I1), IC48.13 (I1), IC102.5 (1Q3), IC102.43 (1D4)
unnamed: IC49.2 (I1), IC49.5 (I1), IC49.10 (I1), IC49.13 (I1), IC50.2 (I1), IC50.5 (I1), IC50.10 (I1), IC50.13 (I1), IC102.6 (1Q4), IC102.41 (1D5), X11.1
unnamed: IC101.25 (2CLK), IC101.48 (1CLK), IC102.25 (2CLK), IC102.48 (1CLK), X11.6
unnamed: IC1.25 (2CLK), IC1.48 (1CLK), IC3.25 (2CLK), IC3.48 (1CLK), IC8.25 (2CLK), IC8.48 (1CLK), IC16.25 (2CLK), IC16.48 (1CLK), IC21.25 (2CLK), IC21.48 (1CLK), IC26.25 (2CLK), IC26.48 (1CLK), IC41.25 (2CLK), IC41.48 (1CLK), IC46.25 (2CLK), IC46.48 (1CLK), IC51.25 (2CLK), IC51.48 (1CLK), IC56.25 (2CLK), IC56.48 (1CLK), X11.5
VCC: IC1.7 (VCC), IC1.18 (VCC), IC1.31 (VCC), IC1.42 (VCC), IC2.14 (VCC), IC3.7 (VCC), IC3.18 (VCC), IC3.31 (VCC), IC3.42 (VCC), IC4.14 (VCC), IC5.14 (VCC), IC6.14 (VCC), IC7.14 (VCC), IC8.7 (VCC), IC8.18 (VCC), IC8.31 (VCC), IC8.42 (VCC), IC9.14 (VCC), IC10.14 (VCC), IC11.14 (VCC), IC12.14 (VCC), IC13.14 (VCC), IC14.14 (VCC), IC15.14 (VCC), IC16.7 (VCC), IC16.18 (VCC), IC16.31 (VCC), IC16.42 (VCC), IC17.14 (VCC), IC18.14 (VCC), IC19.14 (VCC), IC20.14 (VCC), IC21.7 (VCC), IC21.18 (VCC), IC21.31 (VCC), IC21.42 (VCC), IC22.14 (VCC), IC23.14 (VCC), IC24.14 (VCC), IC25.14 (VCC), IC26.7 (VCC), IC26.18 (VCC), IC26.31 (VCC), IC26.42 (VCC), IC27.14 (VCC), IC28.14 (VCC), IC29.14 (VCC), IC30.14 (VCC), IC41.7 (VCC), IC41.18 (VCC), IC41.31 (VCC), IC41.42 (VCC), IC42.14 (VCC), IC43.14 (VCC), IC44.14 (VCC), IC45.14 (VCC), IC46.7 (VCC), IC46.18 (VCC), IC46.31 (VCC), IC46.42 (VCC), IC47.14 (VCC), IC48.14 (VCC), IC49.14 (VCC), IC50.14 (VCC), IC51.7 (VCC), IC51.18 (VCC), IC51.31 (VCC), IC51.42 (VCC), IC52.14 (VCC), IC53.14 (VCC), IC54.14 (VCC), IC55.14 (VCC), IC56.7 (VCC), IC56.18 (VCC), IC56.31 (VCC), IC56.42 (VCC), IC57.14 (VCC), IC58.14 (VCC), IC59.14 (VCC), IC60.14 (VCC), IC101.7 (VCC), IC101.18 (VCC), IC101.31 (VCC), IC101.42 (VCC), IC102.7 (VCC), IC102.18 (VCC), IC102.31 (VCC), IC102.42 (VCC), X11.8

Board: 2 copper layers, 78 parts (0 on the bottom side), 507 nets, no tracks yet.
